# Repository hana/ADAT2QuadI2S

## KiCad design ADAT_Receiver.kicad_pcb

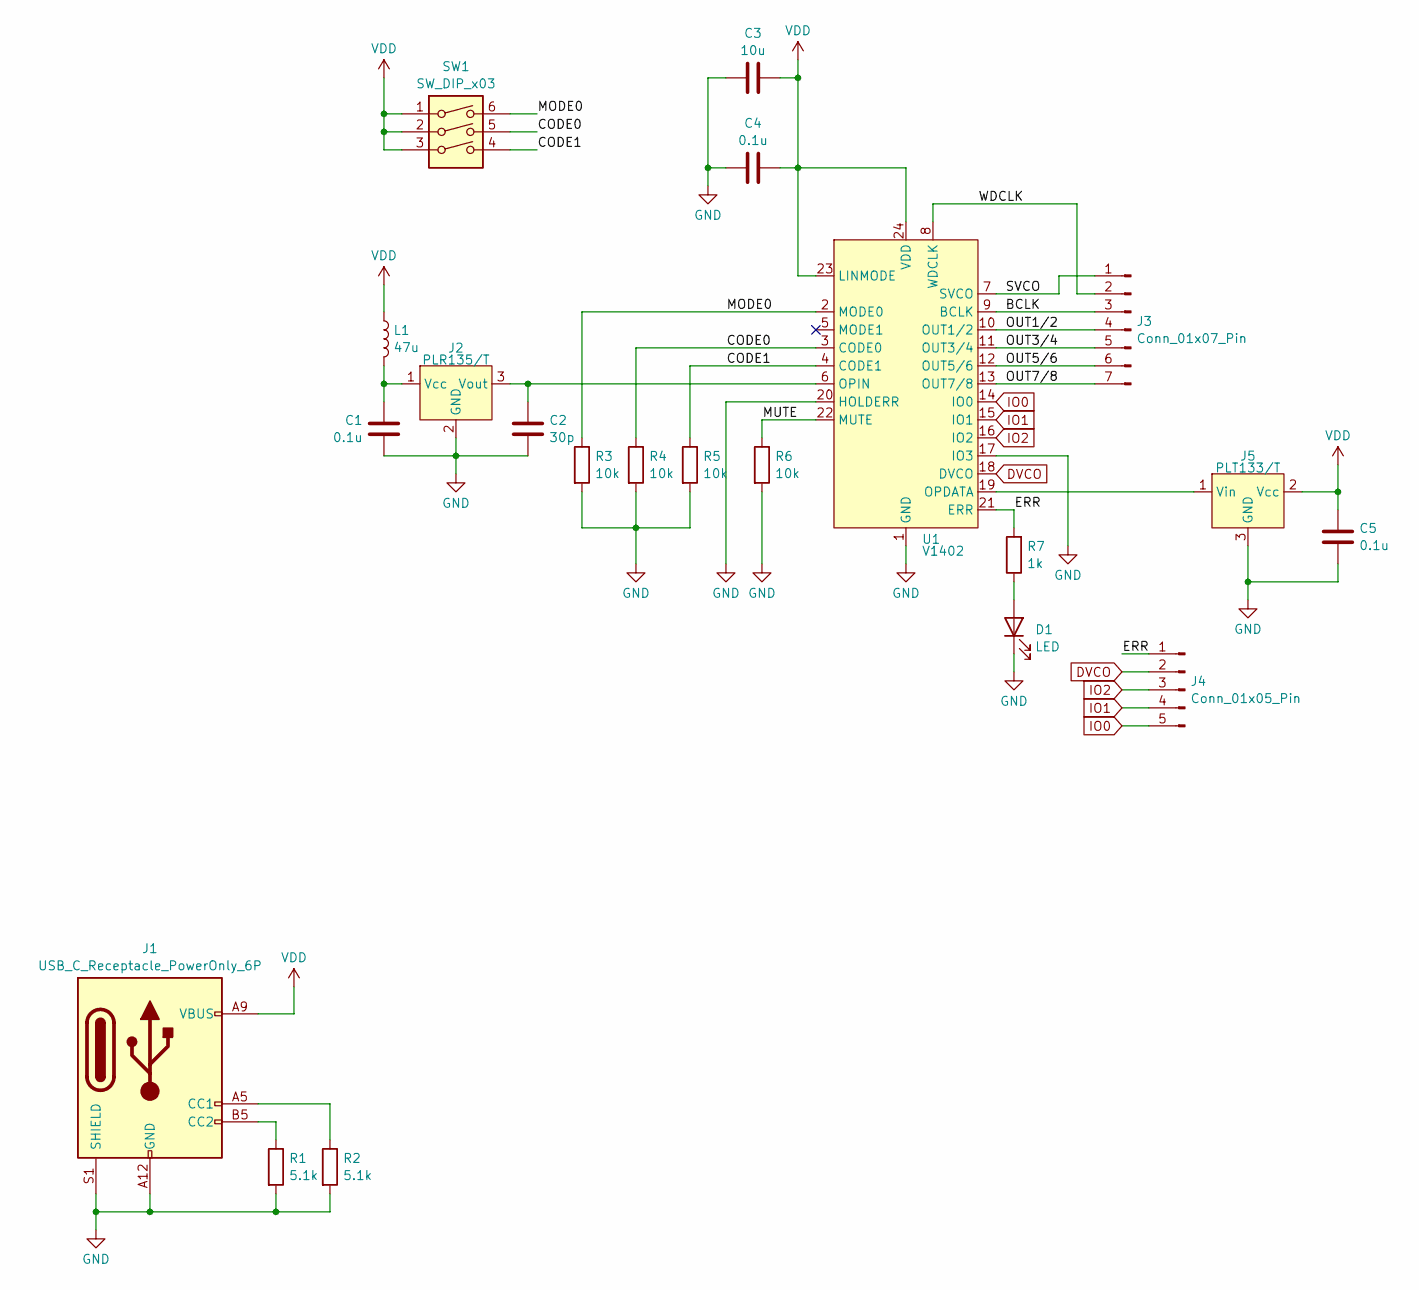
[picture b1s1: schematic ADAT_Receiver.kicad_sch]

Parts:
C1, C4, C5: 0.1u; C_0402_1005Metric; LCSC C1525
C2: 30p; C_0603_1608Metric; LCSC C1658
C3: 10u; C_0603_1608Metric; LCSC C19702
D1: LED; LED_0603_1608Metric; LCSC C2286
J1: USB_C_Receptacle_PowerOnly_6P; USB_C_Receptacle_GCT_USB4125-xx-x_6P_TopMnt_Horizontal; LCSC C668623
J2: PLR135/T; PLx13xT
J3: Conn_01x07_Pin; PinHeader_1x07_P2.54mm_Vertical
J4: Conn_01x05_Pin; PinHeader_1x05_P2.54mm_Vertical
J5: PLT133/T; PLx13xT
L1: 47u; L_0805_2012Metric; LCSC C14304
R1, R2: 5.1k; R_0603_1608Metric; LCSC C23186
R3, R4, R5, R6: 10k; R_0603_1608Metric; LCSC C25804
R7: 1k; R_0603_1608Metric; LCSC C21190
SW1: SW_DIP_x03; SW_DIP_SPSTx03_Slide_6.7x9.18mm_W8.61mm_P2.54mm_LowProfile; LCSC C7421520
U1: V1402; SOP-24_7.5x15.4mm_P1.27mm

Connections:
/BCLK: J3.3, U1.9 (BCLK)
/CODE0: R4.1, SW1.5, U1.3 (CODE0)
/CODE1: R5.1, SW1.4, U1.4 (CODE1)
/ERR: J4.1, R7.2, U1.21 (ERR)
/MODE0: R3.1, SW1.6, U1.2 (MODE0)
/MUTE: R6.1, U1.22 (MUTE)
/OUT1/2: J3.4, U1.10 (OUT1/2)
/OUT3/4: J3.5, U1.11 (OUT3/4)
/OUT5/6: J3.6, U1.12 (OUT5/6)
/OUT7/8: J3.7, U1.13 (OUT7/8)
/SVCO: J3.1, U1.7 (SVCO)
/WDCLK: J3.2, U1.8 (WDCLK)
DVCO: J4.2, U1.18 (DVCO)
GND: C1.2, C2.2, C3.1, C4.1, C5.1, D1.1 (K), J1.A12 (GND), J1.B12 (GND), J1.S1 (SHIELD), J2.2 (GND), J5.3 (GND), R1.2, R2.2, R3.2, R4.2, R5.2, R6.2, U1.1 (GND), U1.17 (IO3), U1.20 (HOLDERR)
IO0: J4.5, U1.14 (IO0)
IO1: J4.4, U1.15 (IO1)
IO2: J4.3, U1.16 (IO2)
unnamed: D1.2 (A), R7.1
unnamed: J1.A5 (CC1), R2.1
unnamed: J1.B5 (CC2), R1.1
unnamed: C1.1, J2.1 (Vcc), L1.2
unnamed: C2.1, J2.3 (Vout), U1.6 (OPIN)
unnamed: J5.1 (Vin), U1.19 (OPDATA)
VDD: C3.2, C4.2, C5.2, J1.A9 (VBUS), J1.B9 (VBUS), J5.2 (Vcc), L1.1, SW1.1, SW1.2, SW1.3, U1.23 (LINMODE), U1.24 (VDD)

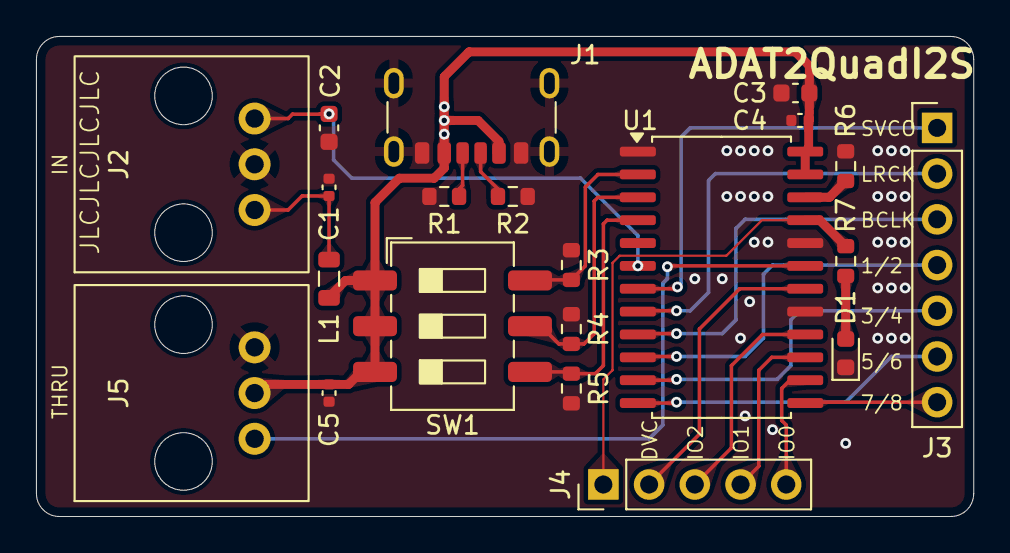
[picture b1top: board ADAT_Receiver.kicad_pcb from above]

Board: 2 copper layers, 52.1 x 26.7 mm, 21 parts (0 on the bottom side), 24 nets.

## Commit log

2025-05-12 remove backup files
2025-05-13 First order
2025-05-13 Moved to ht library
2025-05-31 Fixed photolink receiver pin assign
